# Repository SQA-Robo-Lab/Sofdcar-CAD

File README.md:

# Sofdcar CAD Repository
Contains all relevant CAD files that were created in the context of or as need for the sofdcar project

## Folders
### LinesPrintTemplate
Svg templates for printing different types of lines fo the car to follow.
Are compatible with each other to allow for any track layout desired

#### Manufacturing: Print
- Use specified paper size (A4 if not specified)

### PiCarX
All Cad files for modifying the PiCarX to work with our hardware stack.
I.e. allow for the bigger battery, the Arduinos (Nano and Uno/Mega) and the ESP to be placed atop

### PiCarX/HBridgeMount
Mount for the H-Bridge motor driver board to be mounted underneath the base of the PiCarX.
Allows the motor to svivel to access the connections.

#### Manufacturing: 3D-Print
- Print "Top" Part of sviveling pillar
- Then print "Bottom" part, pause the print before the axle is expanding and insert the "Top" part to interlock them

### PiCarX/NewMegaBox
"Rack" box for mounting the battery, Arduino Nano, ESP and Arduino MEGA to the PiCarX.
Original drawing in `NewCarBox.FCStd`, cross-sections of parts to cut in seperate svg files
(New variant of steered car)

#### Manufacturing: Lasercut + Glue
- Use 3mm Material
- `AssembledLaserFile.svg` already contains all parts closely packed, ready to cut
- Glue all parts into a box except the "CoverPlateAkku" and the "TopPlate" to access the battery and Arduino Nano on the lower levels
- Slide in the "CoverPlateAkku" from the back

### PiCarX/OldUnoBox
Box to house the battery and a breadoard with Arduino Nano, ESP and motor driver as well as the Arduino UNO on top.
(Old variant of steered car)

#### Manufacturing: Lasercut + Glue
- Use 3mm Material
- Cut 2 copies of the Top/Bottom Plate (top middle)
- Cut 2 copies of the front/back part (bottom left)
- Cut 4 copies of the side part (bottom right)
- Glue all parts together into a box except the top plate to access the battery

## File Types
### pdf (gitignored by default)
- Most common type: 2D Export of some other drawing
- Software: Any PDF viewer

### svg
- Most common type: 2D Vectorgraphics, drawn or exported
- Software: [Inkscape](https://inkscape.org/)

### FCStd
- Most common type: (Parametric) 3D CAD drawing
- Software: [FreeCAD](https://www.freecad.org/)

### stl (gitignored by default)
- Most common type: Export of a 3D object from a CAD drawing
- Software (edit): [FreeCAD](https://www.freecad.org/) or [Blender](https://www.blender.org/)
- Software (3d-print): Any slicer (e.g. [PrusaSlicer](https://github.com/prusa3d/PrusaSlicer))

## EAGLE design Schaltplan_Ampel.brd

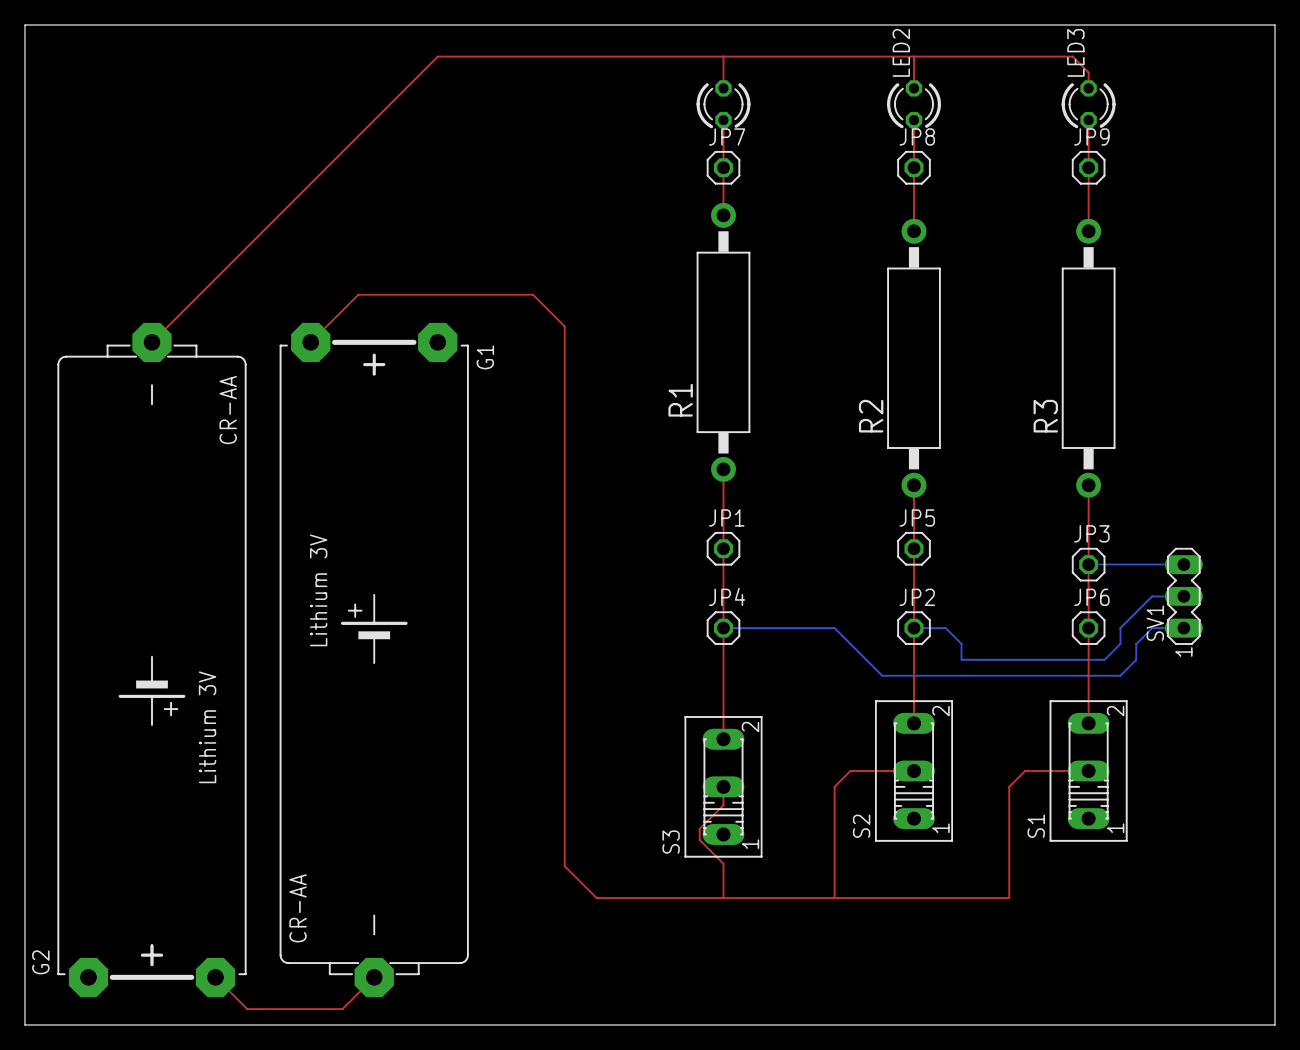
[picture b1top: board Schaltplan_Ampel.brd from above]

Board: 2 copper layers, 100.0 x 80.0 mm, 21 parts (0 on the bottom side), 9 nets.

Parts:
G1, G2: CR-AA; CRAA
JP1, JP2, JP3, JP4, JP5, JP6, JP7, JP8, JP9: 1X01
LED1, LED2, LED3: LED3MM
R1, R2, R3: CA0002
S1, S2, S3: 255SB
SV1: MA03-1

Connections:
unnamed: G1.-, G2.+
unnamed: G1.+, S1.2, S2.2, S3.2
unnamed: G2.-, LED1.K, LED2.K, LED3.K
unnamed: JP3.1, JP6.1, R3.1, S1.3, SV1.3
unnamed: JP2.1, JP5.1, R2.1, S2.3, SV1.2
unnamed: JP1.1, JP4.1, R1.1, S3.3, SV1.1
unnamed: JP7.1, LED1.A, R1.2
unnamed: JP8.1, LED2.A, R2.2
unnamed: JP9.1, LED3.A, R3.2

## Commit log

2023-07-24 Added gitigonre
2023-07-24 Added old cad documents
2023-07-25 Added pdfs generated from inkscape to ignore
2023-07-25 Added Printable line segments svg
2023-07-25 Added first version of box for picarx with arduino mega
2023-07-25 Added first version of hinging mount for hbridge
2023-07-25 Added readme and ignored all pdfs
2023-07-25 Changed formatting
2023-07-27 First revision finished laser file
2023-07-27 Second revision of box
2023-08-14 New iteration of box
2023-08-14 Iteration of hbridge mount
2023-10-16 Moved street elements
2023-11-20 Added older elements for track
2023-11-20 Started work on cnc track
2024-01-22 First cnc-able rev of street
2024-06-21 Added combined laser files, new laser file dir
2024-06-21 Added new ignores, commented gitignore
2024-06-21 Commented gitignore
2024-06-21 Added exported filed for carpenters to cnc the track
2024-06-21 Created schematic of current PiCarX setup
2024-06-21 Optimized connector dimensions based on CNCed elements
2024-08-14 added more A3 track lineprints
2024-08-24 Inlay for CNCed lines to color them
2024-09-11 Seitlicher Mount für Ultraschallsensor am PiXCar
2024-10-31 Line Inlay for painting Wood track
2024-11-04 Switches and compensation pieces
2024-11-04 Export of newest version of cnc track
2024-11-04 Added Kurve18-300 as compensation to 90 deg
